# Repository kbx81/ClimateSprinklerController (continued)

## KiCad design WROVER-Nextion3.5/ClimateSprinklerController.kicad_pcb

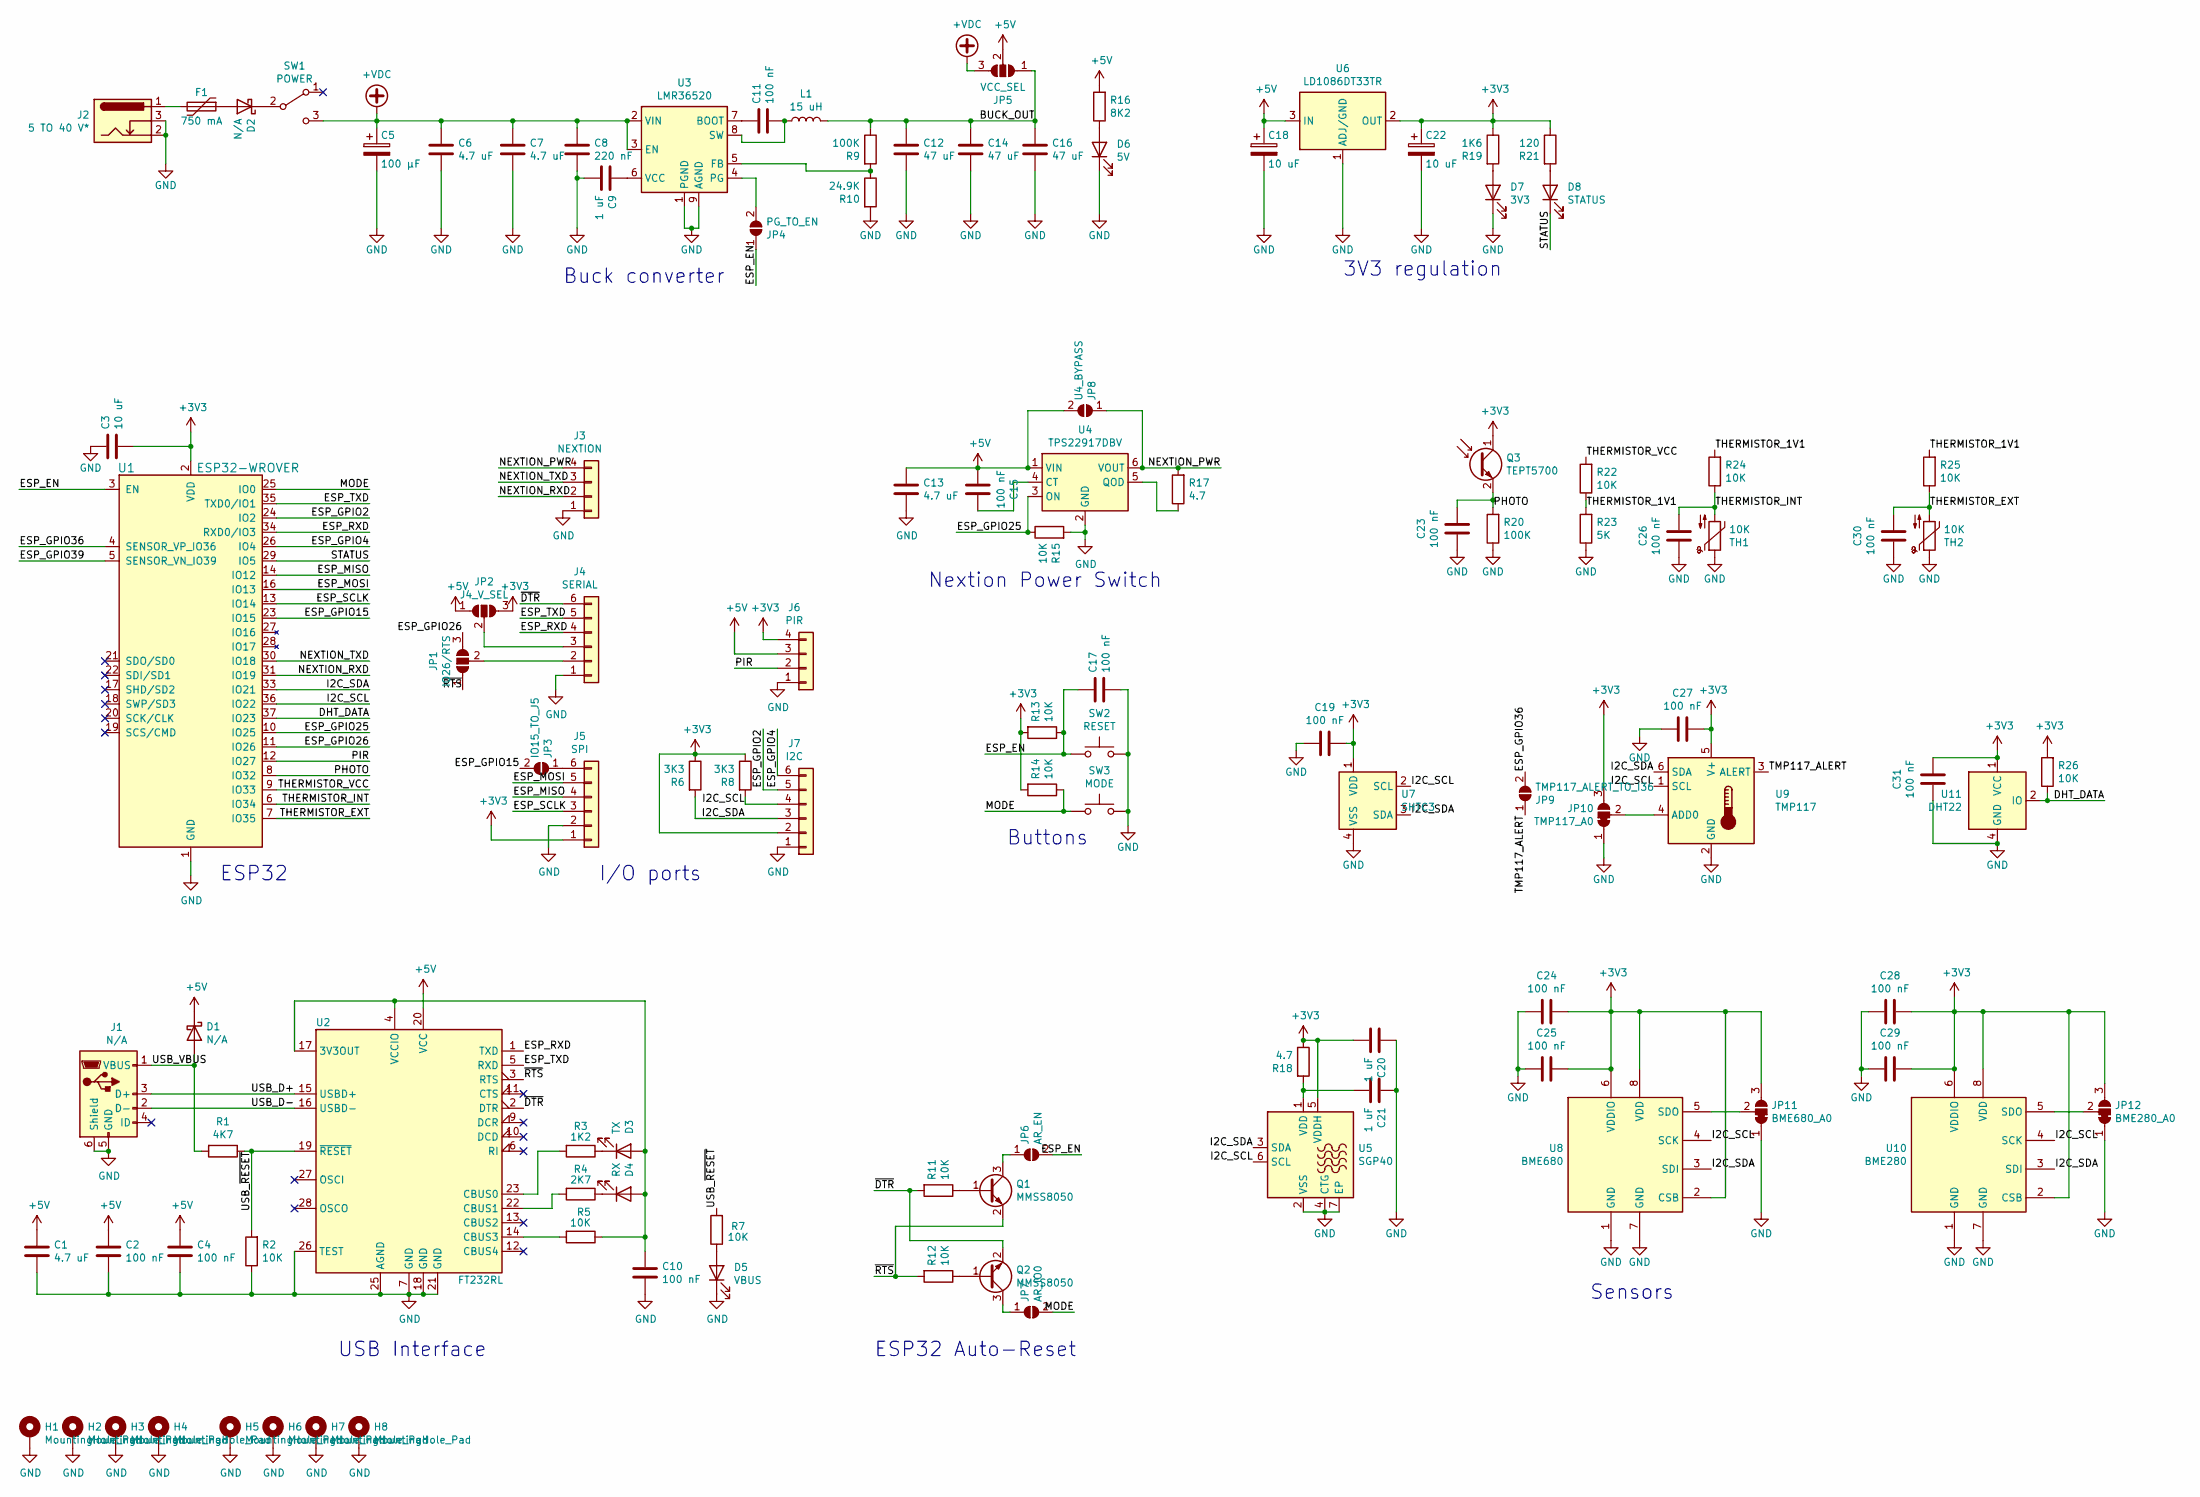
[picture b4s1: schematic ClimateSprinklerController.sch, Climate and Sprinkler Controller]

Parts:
C1, C6, C7, C13: 4.7 uF; C_0805_2012Metric; MPN1 C2012X5R1H475K125AB
C2, C4, C10, C11, C15, C17, C19, C23, C24, C25, C26, C27, C28, C29, C30, C31: 100 nF; C_0805_2012Metric; MPN1 CC0805KRX7R7BB104
C3: 10 uF; C_0805_2012Metric; MPN1 C2012X5R1V106K085AC
C5: 100 µF; CP_Elec_8x10; MPN1 25SVF100M
C8: 220 nF; C_0805_2012Metric; MPN1 C2012X5R1H224K125AA
C9, C20, C21: 1 uF; C_0805_2012Metric; MPN1 C0805C105K4RACTU
C12, C14, C16: 47 uF; C_1210_3225Metric; MPN1 GRM32ER61C476KE15L
C18, C22: 10 uF; CP_Elec_5x5.8; MPN1 EEE-HP0J100R
D1, D2: N/A; D_SOD-123F; MPN1 MBR230S1F-7
D3: TX; LED_1206_3216Metric_ReverseMount_Hole1.8x2.4mm; MPN1 APTL3216QBC/D
D4: RX; LED_1206_3216Metric_ReverseMount_Hole1.8x2.4mm; MPN1 APTL3216SURCK
D5: VBUS; LED_1206_3216Metric_ReverseMount_Hole1.8x2.4mm; MPN1 APTL3216ZGC
D6: 5V; LED_1206_3216Metric_ReverseMount_Hole1.8x2.4mm; MPN1 597-6901-607F
D7: 3V3; LED_1206_3216Metric_ReverseMount_Hole1.8x2.4mm; MPN1 597-6901-607F
D8: STATUS; LED_1206_3216Metric_ReverseMount_Hole1.8x2.4mm; MPN1 APTL3216SECK
F1: 750 mA; Fuse_2920_7451Metric; MPN1 2920L075
H1, H2, H3, H4: MountingHole_Pad; MountingHole_3.2mm_M3_Pad_Via; MPN1 N/A
H5, H6, H7, H8: MountingHole_Pad; MountingHole_3.2mm_M3_DIN965_Pad; MPN1 N/A
J1: N/A; USB_Micro-B_Molex-105017-0001; MPN1 105017-0001
J2: 5 TO 40 V*; BarrelJack_Horizontal; MPN1 694106301002
J3: NEXTION; PinSocket_1x04_P2.54mm_Vertical; MPN1 N/A
J4: SERIAL; PinSocket_1x06_P2.54mm_Vertical; MPN1 N/A
J5: SPI; PinSocket_1x06_P2.54mm_Vertical; MPN1 N/A
J6: PIR; PinSocket_1x04_P2.54mm_Vertical; MPN1 N/A
J7: I2C; PinSocket_1x06_P2.54mm_Vertical; MPN1 N/A
JP1: IO26/RTS; SolderJumper-3_P1.3mm_Open_RoundedPad1.0x1.5mm; MPN1 N/A
JP2: J4_V_SEL; SolderJumper-3_P1.3mm_Open_RoundedPad1.0x1.5mm; MPN1 N/A
JP3: IO15_TO_J5; SolderJumper-2_P1.3mm_Open_RoundedPad1.0x1.5mm; MPN1 N/A
JP4: PG_TO_EN; SolderJumper-2_P1.3mm_Open_RoundedPad1.0x1.5mm; MPN1 N/A
JP5: VCC_SEL; SolderJumper-3_P1.3mm_Open_RoundedPad1.0x1.5mm; MPN1 N/A
JP6: AR_EN; SolderJumper-2_P1.3mm_Open_RoundedPad1.0x1.5mm; MPN1 N/A
JP7: AR_IO0; SolderJumper-2_P1.3mm_Open_RoundedPad1.0x1.5mm; MPN1 N/A
JP8: U4_BYPASS; SolderJumper-2_P1.3mm_Open_RoundedPad1.0x1.5mm; MPN1 N/A
JP9: TMP117_ALERT_TO_I36; SolderJumper-2_P1.3mm_Open_RoundedPad1.0x1.5mm; MPN1 N/A
JP10: TMP117_A0; SolderJumper-3_P1.3mm_Bridged12_RoundedPad1.0x1.5mm; MPN1 N/A
JP11: BME680_A0; SolderJumper-3_P1.3mm_Bridged12_RoundedPad1.0x1.5mm; MPN1 N/A
JP12: BME280_A0; SolderJumper-3_P1.3mm_Bridged12_RoundedPad1.0x1.5mm; MPN1 N/A
L1: 15 uH; L_Wuerth_WE-PD-Typ-LS; MPN1 7447709150
Q1, Q2: MMSS8050; SOT-23; MPN1 MMSS8050
Q3: TEPT5700; LED_D5.0mm_Clear; MPN1 TEPT5700
R1: 4K7; R_0805_2012Metric_Pad1.20x1.40mm_HandSolder; MPN1 RT0805FRE074K7L
R2, R5, R7, R11, R12, R13, R14, R15, R22, R24, R25, R26: 10K; R_0805_2012Metric_Pad1.20x1.40mm_HandSolder; MPN1 RC0805FR-0710KL
R3: 1K2; R_0805_2012Metric_Pad1.20x1.40mm_HandSolder; MPN1 RT0805FRE072K7L
R4: 2K7; R_0805_2012Metric_Pad1.20x1.40mm_HandSolder; MPN1 RT0805FRE072K7L
R6, R8: 3K3; R_0805_2012Metric_Pad1.20x1.40mm_HandSolder; MPN1 RT0805FRE073K3L
R9, R20: 100K; R_0805_2012Metric_Pad1.20x1.40mm_HandSolder; MPN1 RC0805FR-07100KL
R10: 24.9K; R_0805_2012Metric_Pad1.20x1.40mm_HandSolder; MPN1 RT0805FRE0724K9L
R16: 8K2; R_0805_2012Metric_Pad1.20x1.40mm_HandSolder; MPN1 RT0805FRE078K2L
R17, R18: 4.7; R_0805_2012Metric_Pad1.20x1.40mm_HandSolder; MPN1 RC0805FR-074R7L
R19: 1K6; R_0805_2012Metric_Pad1.20x1.40mm_HandSolder; MPN1 RT0805FRE071K6L
R21: 120; R_0805_2012Metric_Pad1.20x1.40mm_HandSolder; MPN1 RT0805FRE07120RL
R23: 5K; R_0805_2012Metric_Pad1.20x1.40mm_HandSolder; MPN1 CRCW08055K00JNTA
SW1: POWER; SW_Push_1P2T_Vertical_E-Switch_800UDP8P1A1M6; MPN1 48BFSP1M6QT
SW2: RESET; SW_Tactile_SPST_Angled_PTS645Vx58-2LFS; MPN1 PTS645VK582LFS
SW3: MODE; SW_Tactile_SPST_Angled_PTS645Vx58-2LFS; MPN1 PTS645VK582LFS
TH1, TH2: 10K; PinSocket_1x02_P2.54mm_Vertical; MPN1 NXFT15XH103FA2B100
U1: ESP32-WROVER; MPN1 ESP32-WROVER
U2: FT232RL; SSOP-28_5.3x10.2mm_P0.65mm; MPN1 FT232RL
U3: LMR36520; Texas_HSOP-8-1EP_3.9x4.9mm_P1.27mm_ThermalVias; MPN1 LMR36520ADDAR
U4: TPS22917DBV; SOT-23-6; MPN1 TPS22917DBV
U5: SGP40; DFN-6-1EP_2.44x2.44mm_P0.8mm_EP1.25x1.7mm; MPN1 SGP40
U6: LD1086DT33TR; TO-252-2; MPN1 LD1086DT33TR
U7: SHTC3; AMS_QFN-4-1EP_2x2mm_P0.95mm_EP0.7x1.6mm; MPN1 SHTC3
U8: BME680; Bosch_LGA-8_3x3mm_P0.8mm_ClockwisePinNumbering; MPN1 BME680
U9: TMP117; WSON-6-1EP_2x2mm_P0.65mm_EP1x1.6mm; MPN1 TMP117MAIDRVR
U10: BME280; Bosch_LGA-8_2.5x2.5mm_P0.65mm_ClockwisePinNumbering; MPN1 BME280
U11: DHT22; PinSocket_1x04_P2.54mm_Vertical; MPN1 DHT22

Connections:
+3V3: C3.2, C19.1, C20.2, C22.1, C24.1, C25.1, C27.1, C28.1, C29.1, C31.1, J5.1, J6.4, J7.2, JP2.3 (B), JP10.3 (B), JP11.3 (B), JP12.3 (B), Q3.1 (C), R6.1, R8.1, R13.2, R14.2, R18.1, R19.1, R21.1, R26.2, U1.2 (VDD), U5.5 (VDDH), U6.2 (OUT), U7.1 (VDD), U8.2 (CSB), U8.6 (VDDIO), U8.8 (VDD), U9.5 (V+), U10.2 (CSB), U10.6 (VDDIO), U10.8 (VDD), U11.1 (VCC)
+5V: C1.1, C2.1, C4.1, C13.1, C15.2, C18.1, D1.1 (K), J6.3, JP2.1 (A), JP5.2 (C), JP8.2 (B), R16.2, U2.20 (VCC), U4.1 (VIN), U6.3 (IN)
+VDC: C5.1, C6.1, C7.1, C8.1, JP5.3 (B), SW1.3 (C), U3.2 (VIN), U3.3 (EN)
/BUCK_OUT: C12.1, C14.1, C16.1, JP5.1 (A), L1.2, R9.1
/DHT_DATA: R26.1, U1.37 (IO23), U11.2 (IO)
/ESP_EN: C17.1, JP4.1 (A), JP6.2 (B), R13.1, SW2.2, U1.3 (EN)
/ESP_GPIO2: J7.5, U1.24 (IO2)
/ESP_GPIO4: J7.6, U1.26 (IO4)
/ESP_GPIO15: JP3.2 (B), U1.23 (IO15)
/ESP_GPIO25: R15.1, U1.10 (IO25), U4.3 (ON)
/ESP_GPIO26: JP1.3 (B), U1.11 (IO26)
/ESP_GPIO36: JP9.2 (B), U1.4 (SENSOR_VP_IO36)
/ESP_MISO: J5.4, U1.14 (IO12)
/ESP_MOSI: J5.5, U1.16 (IO13)
/ESP_RXD: J4.4, U1.34 (RXD0/IO3), U2.1 (TXD)
/ESP_SCLK: J5.3, U1.13 (IO14)
/ESP_TXD: J4.5, U1.35 (TXD0/IO1), U2.5 (RXD)
/I2C_SCL: J7.4, R8.2, U1.36 (IO22), U5.6 (SCL), U7.2 (SCL), U8.4 (SCK), U9.1 (SCL), U10.4 (SCK)
/I2C_SDA: J7.3, R6.2, U1.33 (IO21), U5.3 (SDA), U7.3 (SDA), U8.3 (SDI), U9.6 (SDA), U10.3 (SDI)
/MODE: JP7.2 (B), R14.1, SW3.1, U1.25 (IO0)
/NEXTION_PWR: J3.4, JP8.1 (A), R17.2, U4.6 (VOUT)
/NEXTION_RXD: J3.2, U1.31 (IO19)
/NEXTION_TXD: J3.3, U1.30 (IO18)
/PHOTO: C23.1, Q3.2 (E), R20.2, U1.8 (IO32)
/PIR: J6.2, U1.12 (IO27)
/STATUS: D8.1 (K), U1.29 (IO5)
/THERMISTOR_1V1: R22.1, R23.2, R24.2, R25.2
/THERMISTOR_EXT: C30.1, R25.1, TH2.2, U1.7 (IO35)
/THERMISTOR_INT: C26.1, R24.1, TH1.2, U1.6 (IO34)
/THERMISTOR_VCC: R22.2, U1.9 (IO33)
/TMP117_ALERT: JP9.1 (A), U9.3 (ALERT)
/USB_D+: J1.3 (D+), U2.15 (USBD+)
/USB_D-: J1.2 (D-), U2.16 (USBD-)
/USB_VBUS: D1.2 (A), J1.1 (VBUS), R1.2
/USB_~RESET: R1.1, R2.2, R7.2, U2.19 (~RESET~)
/~DTR: J4.6, Q2.2 (E), R11.2, U2.2 (DTR)
/~RTS: JP1.1 (A), Q1.2 (E), R12.2, U2.3 (RTS)
GND: C1.2, C2.2, C3.1, C4.2, C5.2, C6.2, C7.2, C8.2, C9.2, C10.2, C12.2, C13.2, C14.2, C16.2, C17.2, C18.2, C19.2, C20.1, C21.1, C22.2, C23.2, C24.2, C25.2, C26.2, C27.2, C28.2, C29.2, C30.2, C31.2, D5.1 (K), D6.1 (K), D7.1 (K), H1.1, H2.1, H3.1, H4.1, H5.1, H6.1, H7.1, H8.1, J1.5 (GND), J1.6 (Shield), J2.2, J2.3, J3.1, J4.1, J5.2, J6.1, J7.1, JP10.1 (A), JP11.1 (A), JP12.1 (A), R2.1, R10.2, R15.2, R20.1, R23.1, SW2.1, SW3.2, TH1.1, TH2.1, U1.1 (GND), U1.15 (GND), U1.38 (GND), U1.39 (GND), U2.7 (GND), U2.18 (GND), U2.21 (GND), U2.25 (AGND), U2.26 (TEST), U3.1 (PGND), U3.9 (AGND), U4.2 (GND), U5.2 (VSS), U5.4 (CTG), U5.7 (EP), U6.1 (ADJ/GND), U7.4 (VSS), U8.1 (GND), U8.7 (GND), U9.2 (GND), U10.1 (GND), U10.7 (GND), U11.4 (GND)
unnamed: C9.1, U3.6 (VCC)
unnamed: C10.1, D3.2 (A), D4.2 (A), R5.1, U2.4 (VCCIO), U2.17 (3V3OUT)
unnamed: C11.1, U3.7 (BOOT)
unnamed: C11.2, L1.1, U3.8 (SW)
unnamed: C15.1, U4.4 (CT)
unnamed: C21.2, R18.2, U5.1 (VDD)
unnamed: D2.1 (K), SW1.2 (B)
unnamed: D2.2 (A), F1.1
unnamed: D3.1 (K), R3.1
unnamed: D4.1 (K), R4.1
unnamed: D5.2 (A), R7.1
unnamed: D6.2 (A), R16.1
unnamed: D7.2 (A), R19.2
unnamed: D8.2 (A), R21.2
unnamed: F1.2, J2.1
unnamed: J4.2, JP1.2 (C)
unnamed: J4.3, JP2.2 (C)
unnamed: J5.6, JP3.1 (A)
unnamed: JP4.2 (B), U3.4 (PG)
unnamed: JP6.1 (A), Q1.3 (C)
unnamed: JP7.1 (A), Q2.3 (C)
unnamed: JP10.2 (C), U9.4 (ADD0)
unnamed: JP11.2 (C), U8.5 (SDO)
unnamed: JP12.2 (C), U10.5 (SDO)
unnamed: Q1.1 (B), R11.1
unnamed: Q2.1 (B), R12.1
unnamed: R3.2, U2.23 (CBUS0)
unnamed: R4.2, U2.22 (CBUS1)
unnamed: R5.2, U2.14 (CBUS3)
unnamed: R9.2, R10.1, U3.5 (FB)
unnamed: R17.1, U4.5 (QOD)

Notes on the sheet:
I/O ports
ESP32
Buttons
Sensors
ESP32 Auto-Reset
USB Interface
Nextion Power Switch
3V3 regulation
Buck converter

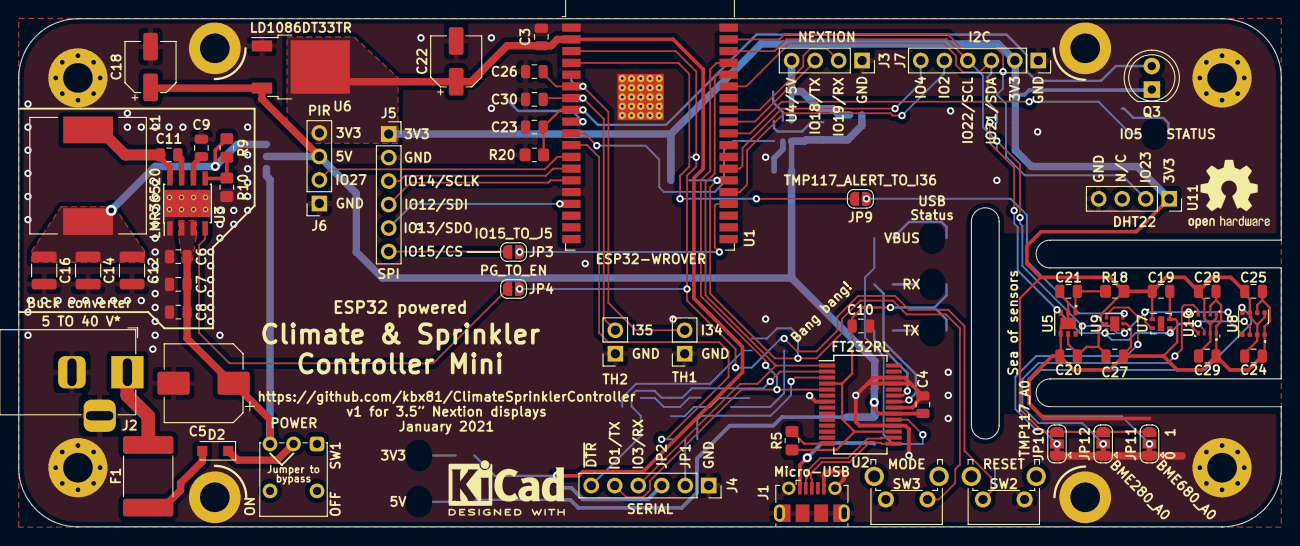
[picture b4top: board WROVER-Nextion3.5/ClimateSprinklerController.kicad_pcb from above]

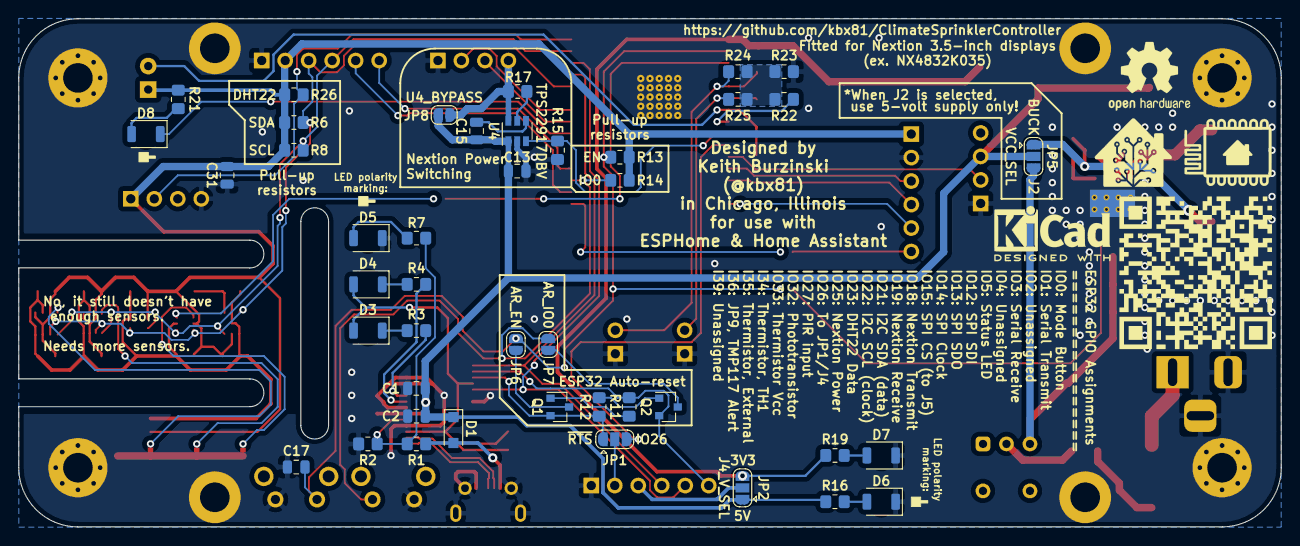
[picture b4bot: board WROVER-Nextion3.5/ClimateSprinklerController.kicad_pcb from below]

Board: 2 copper layers, 136.5 x 54.9 mm, 114 parts (44 on the bottom side), 69 nets.

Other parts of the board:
QR*****: ClimateSprinklerControllerQR

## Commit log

2021-01-25 Nextion PCBs initial commit
2021-01-25 Nextion PCBs tweak
2021-01-25 Remove zip
2021-01-31 TX+RX LEDs were backwards...oops
2021-11-09 Update README.md
    https://forum.kicad.info/t/warning-avoid-all-links-to-kicad-pcb-org-use-kicad-org/31521
2022-01-07 Doc updates, new images, new enclosures, regenerate gerbers
2022-01-08 Update more links
